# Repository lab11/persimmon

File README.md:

# persimmon
platform to test connectivity of cellular networks around the world

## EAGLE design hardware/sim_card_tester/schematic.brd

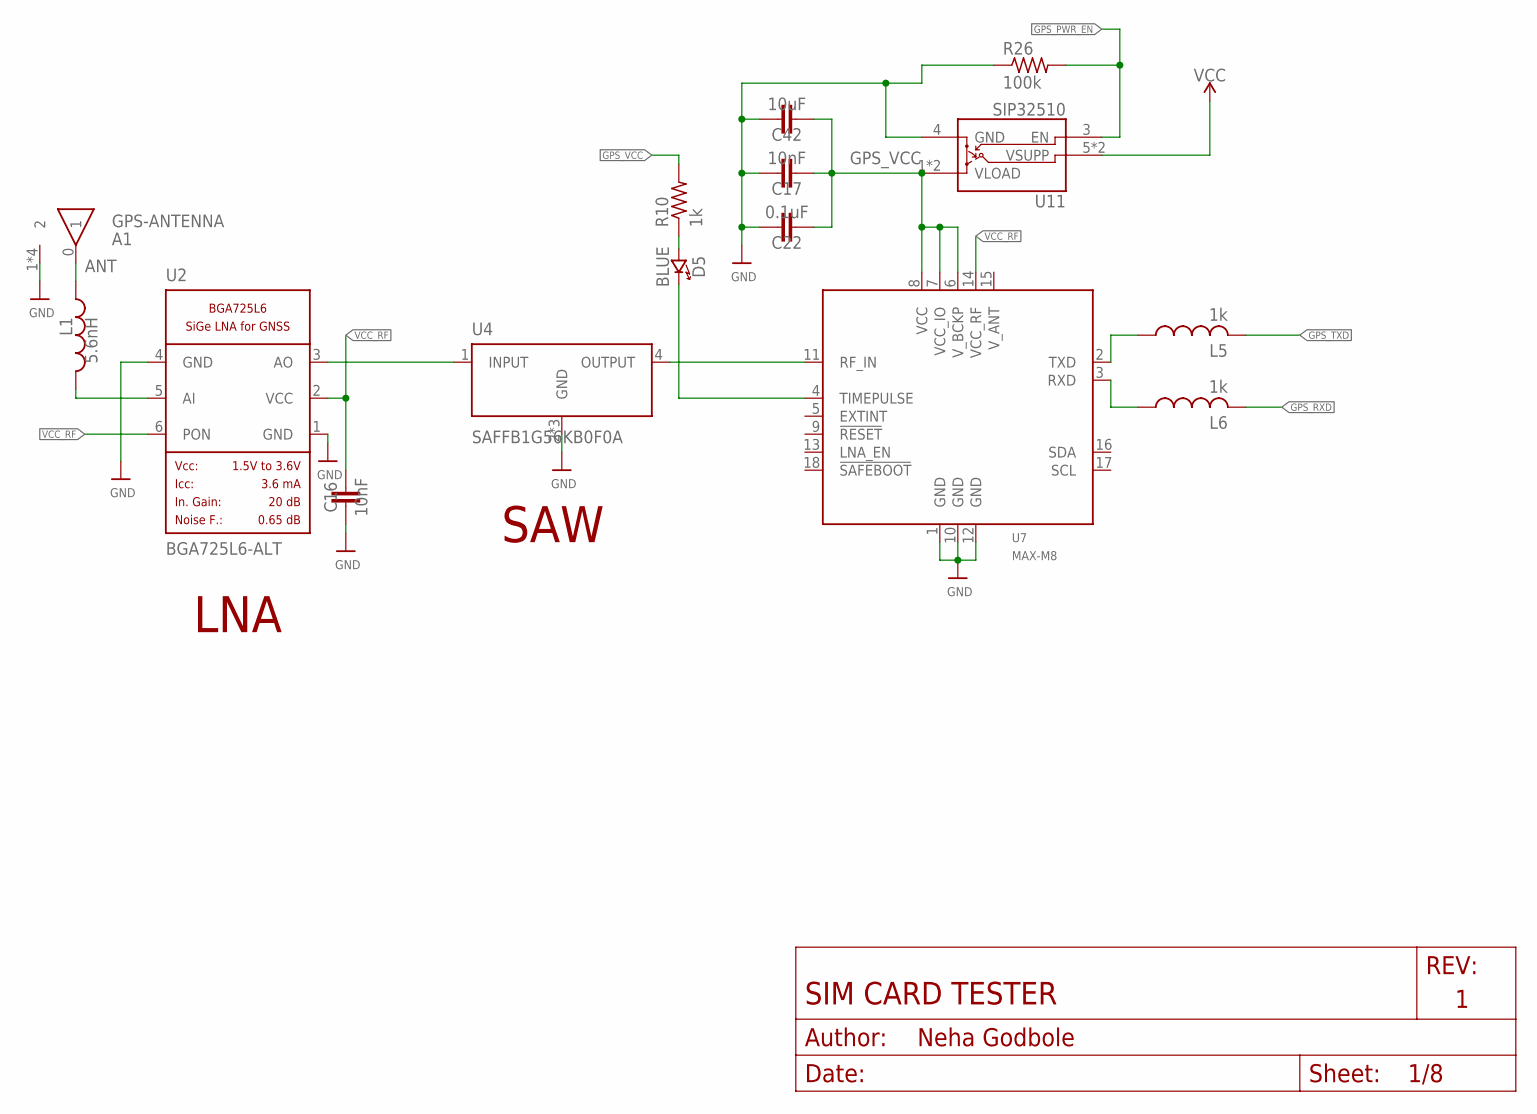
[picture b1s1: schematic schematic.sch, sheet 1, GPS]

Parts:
A1: GPS-ANTENNA; ANT1818B00BT1516S; MPN ANT1818B00BT1516S; DIGIKEY 311-1531-ND
C16, C17: 10nF; RESC0603_L; MPN GRM033R61E103KA12D; DIGIKEY 490-7194-1-ND
C22: 0.1uF; RESC0603_L; MPN GRM033R61A104ME15D; DIGIKEY 490-5405-1-ND
C42: 10uF; RESC0603_L; MPN GRM188R60J106KE47D; DIGIKEY 490-12538-1-ND
D5: BLUE; LED-0603; MPN LTST-C194TBKT; DIGIKEY 160-1837-6-ND
L1: 5.6nH; RESC0603_M; MPN LQW18AN5N6G8ZD; DIGIKEY 490-15723-1-ND
L5, L6: 1k; RESC0603_M; MPN Murata Electronics; DIGIKEY 490-1015-1-ND
R10: 1k; R0603; MPN RC0603JR-071KL; DIGIKEY 311-1.0KGRCT-ND
R26: 100k; R0603; MPN RC0603JR-07100KL; DIGIKEY 311-100KGRCT-ND
U2: BGA725L6-ALT; LNA-TSLP-6-2-ALT; MPN BGA725L6E6327FTSA1; DIGIKEY BGA725L6E6327FTSA1CT-ND
U4: SAFFB1G56KB0F0A; QCS5I; MPN F6QA1G582H2JM-J; DIGIKEY 587-3990-1-ND
U7: MAX-M8; MPN MAX-M8Q-0; DIGIKEY 672-1003-1-ND
U11: SIP32510; TSOT23-6

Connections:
ANT: A1.0 (1), L1.2
GND: A1.1 (2), A1.2, A1.3 (2), A1.4 (2), C16.1, C17.1, C22.1, C42.1, R26.1, U2.1 (GND), U2.4 (GND), U4.2 (GND), U4.3 (GND), U4.5 (GND), U7.1 (GND), U7.10 (GND), U7.12 (GND), U11.4 (GND); also elsewhere on the board
GPS_PWR_EN: R26.2, U11.3 (EN); also elsewhere on the board
GPS_RF_IN: U4.4 (OUTPUT), U7.11 (RF_IN)
GPS_RXD: L6.2; also elsewhere on the board
GPS_TXD: L5.2; also elsewhere on the board
GPS_VCC: C17.2, C22.2, C42.2, R10.2, U7.6 (V_BCKP), U7.7 (VCC_IO), U7.8 (VCC), U11.1 (VLOAD), U11.2 (VLOAD)
LNA_IN: L1.1, U2.5 (AI)
LNA_OUT: U2.3 (AO), U4.1 (INPUT)
unnamed: D5.A (ANODE), R10.1
unnamed: D5.C (CATHODE), U7.4 (TIMEPULSE)
unnamed: L5.1, U7.2 (TXD)
unnamed: L6.1, U7.3 (RXD)
VCC: U11.5 (VSUPP), U11.6 (VSUPP); also elsewhere on the board
VCC_RF: C16.2, U2.2 (VCC), U2.6 (PON), U7.14 (VCC_RF)

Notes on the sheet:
LNA
SAW

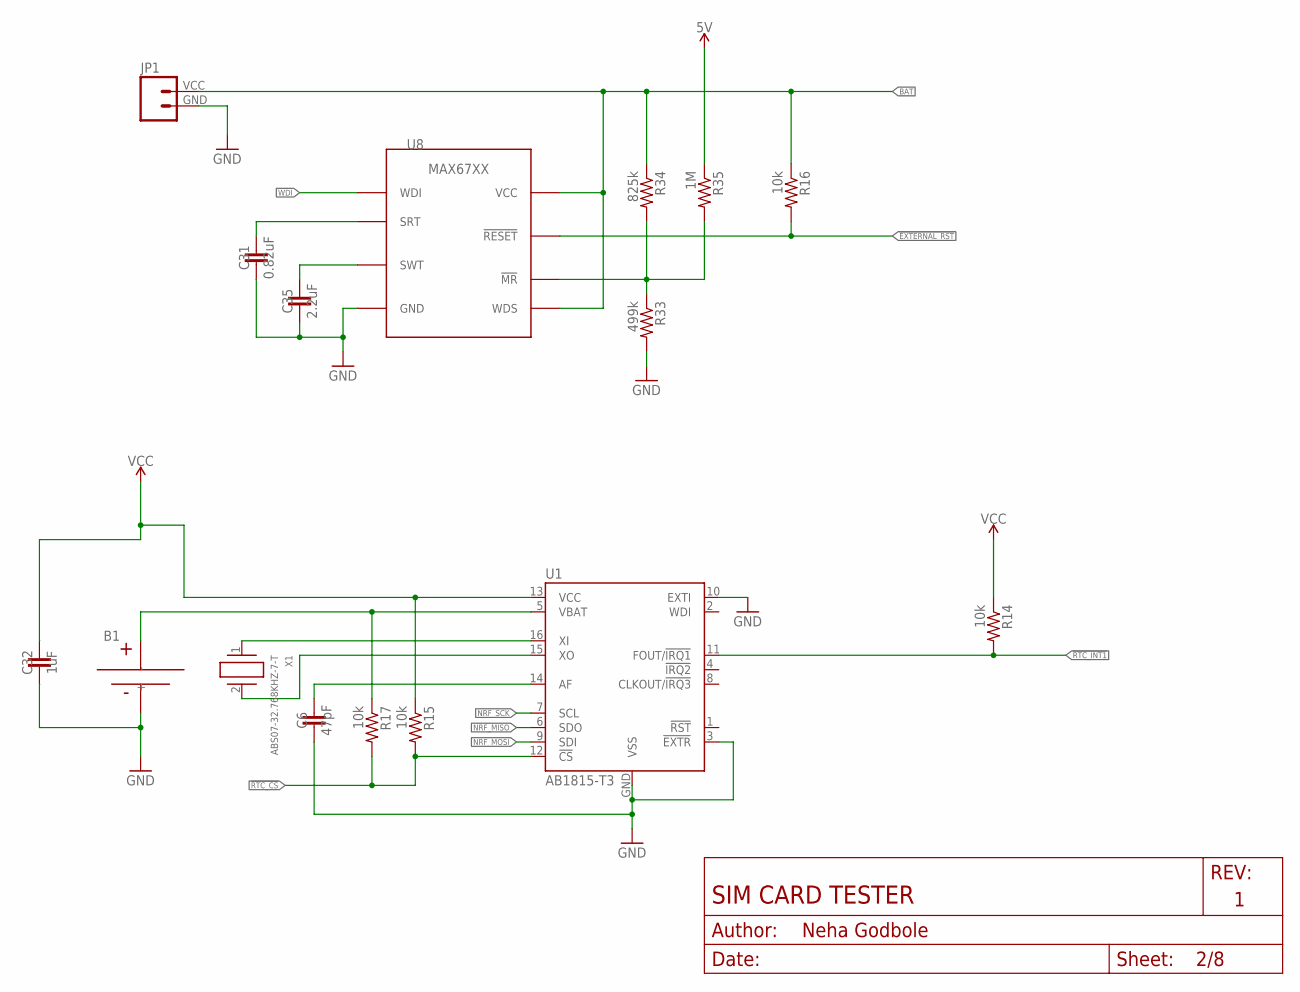
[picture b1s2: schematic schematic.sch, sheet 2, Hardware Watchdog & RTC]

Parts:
B1: MS518SE; MS518SE-FL35E
C6: 47pF; RESC0603_L; MPN C0603C105K8PACTU; DIGIKEY 399-3118-1-ND
C31: 0.82uF; RESC0603_L; MPN C0603C824K8PACTU; DIGIKEY 399-3117-1-ND
C32: 1uF; RESC0603_L; MPN C0603C105K8PACTU; DIGIKEY 399-3118-1-ND
C35: 2.2uF; RESC0603_L; MPN GRM188R61E225MA12D; DIGIKEY 490-12738-1-ND
JP1: M024UCON-15767; JST-2-SMD-VERT; MPN B2B-PH-SM4-TB(LF)(SN); DIGIKEY 455-1734-1-ND
R14, R15, R16, R17: 10k; R0603; MPN RC0603JR-0710KL; DIGIKEY 311-10KGRCT-ND
R33: 499k; R0603; MPN RC0603FR-07499KL; DIGIKEY 311-499KHRCT-ND
R34: 825k; R0603; MPN RC0603FR-07825KL; DIGIKEY 311-825KHRCT-ND
R35: 1M; R0603; MPN RC0603FR-071ML; DIGIKEY 311-1.00MHRCT-ND
U1: AB1815-T3; QFN-16-3MM
U8: MAX67XXMAX6749MAX67XX; SOT-23-8
X1: ABS07-32.768KHZ-7-T; 2-SMD

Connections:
5V: R35.1; also elsewhere on the board
!EXTERNAL_RST: R16.2, U8.7 (!RESET); also elsewhere on the board
!RTC_CS: R15.2, R17.2, U1.12 (!CS); also elsewhere on the board
!RTC_INT1: R14.2, U1.11 (FOUT/!IRQ1); also elsewhere on the board
BAT: JP1.VCC (2), R16.1, R34.1, U8.5 (WDS), U8.8 (VCC); also elsewhere on the board
GND: B1.-, C6.2, C31.2, C32.2, C35.2, JP1.GND (1), R33.2, U1.3 (!EXTR), U1.10 (EXTI), U1.GND (VSS), U8.4 (GND); also elsewhere on the board
unnamed: B1.+, R17.1, U1.5 (VBAT)
unnamed: C6.1, U1.14 (AF)
unnamed: U1.15 (XO), X1.2
unnamed: U1.16 (XI), X1.1
unnamed: R33.1, R34.2, R35.2, U8.1 (!MR)
unnamed: C31.1, U8.3 (SRT)
unnamed: C35.1, U8.2 (SWT)
NRF_MISO: U1.6 (SDO); also elsewhere on the board
NRF_MOSI: U1.9 (SDI); also elsewhere on the board
NRF_SCK: U1.7 (SCL); also elsewhere on the board
VCC: C32.1, R14.1, R15.1, U1.13 (VCC); also elsewhere on the board
WDI: U8.6 (WDI); also elsewhere on the board

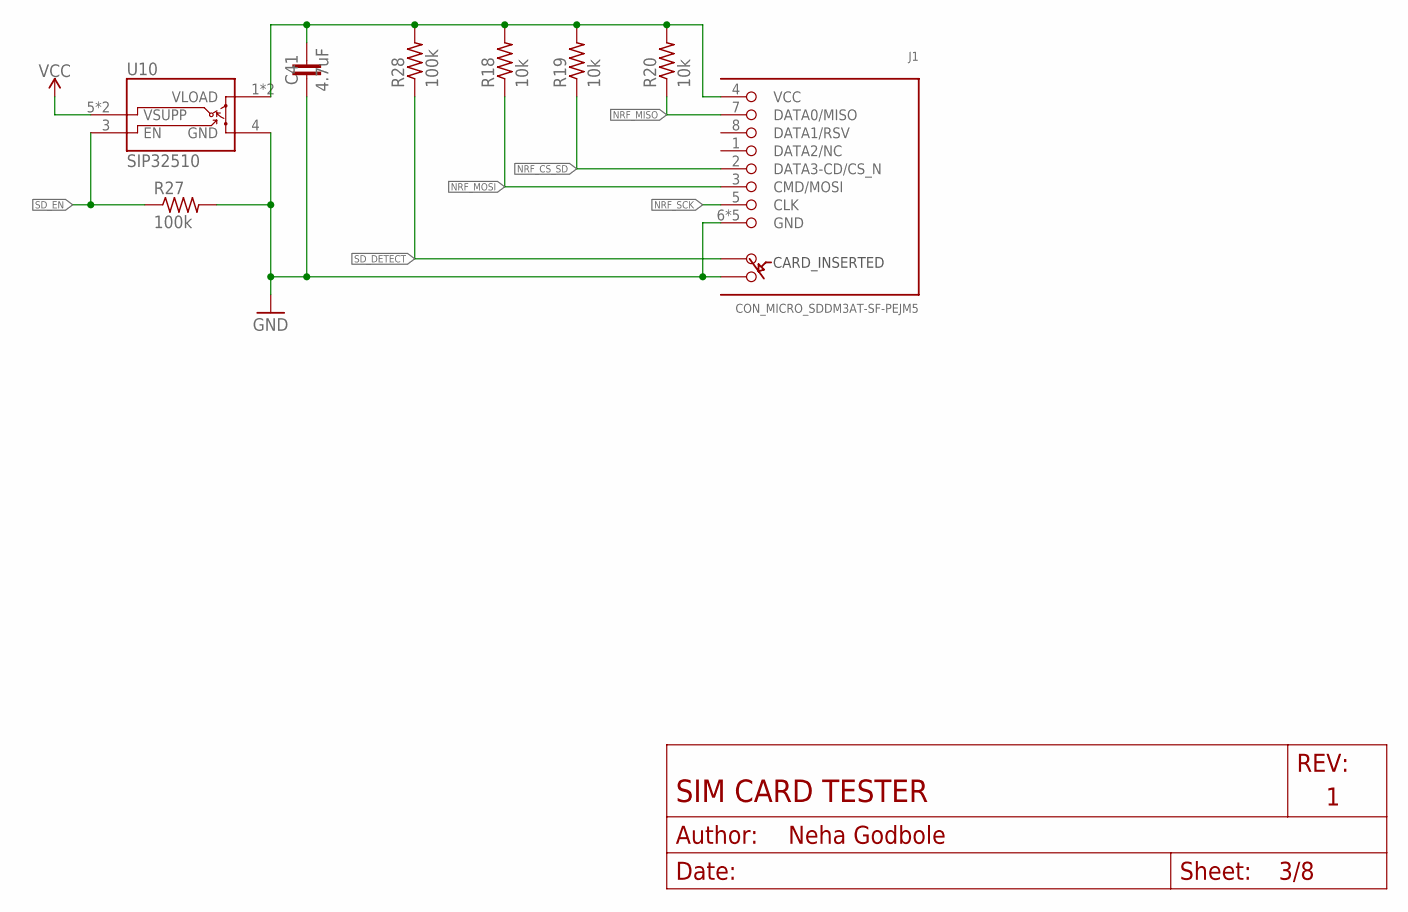
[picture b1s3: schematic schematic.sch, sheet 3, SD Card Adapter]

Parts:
C41: 4.7uF; RESC0603_L; MPN ZRB18AR6YA475KE05L; DIGIKEY 490-10992-1-ND
J1: CON_MICRO_SDDM3AT-SF-PEJM5; DM3AT-SF-PEJM5; MPN DM3AT-SF-PEJM5
R18, R19, R20: 10k; R0603; MPN RC0603JR-0710KL; DIGIKEY 311-10KGRCT-ND
R27, R28: 100k; R0603; MPN RC0603JR-07100KL; DIGIKEY 311-100KGRCT-ND
U10: SIP32510; TSOT23-6

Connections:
!NRF_CS_SD: J1.2 (DATA3-CD/CS_N), R19.1; also elsewhere on the board
!SD_DETECT: J1.A, R28.1; also elsewhere on the board
GND: C41.2, J1.6 (GND), J1.B, J1.MOUNT0 (GND), J1.MOUNT1 (GND), J1.MOUNT2 (GND), J1.MOUNT3 (GND), R27.2, U10.4 (GND); also elsewhere on the board
unnamed: C41.1, J1.4 (VCC), R18.2, R19.2, R20.2, R28.2, U10.1 (VLOAD), U10.2 (VLOAD)
NRF_MISO: J1.7 (DATA0/MISO), R20.1; also elsewhere on the board
NRF_MOSI: J1.3 (CMD/MOSI), R18.1; also elsewhere on the board
NRF_SCK: J1.5 (CLK); also elsewhere on the board
SD_EN: R27.1, U10.3 (EN); also elsewhere on the board
VCC: U10.5 (VSUPP), U10.6 (VSUPP); also elsewhere on the board

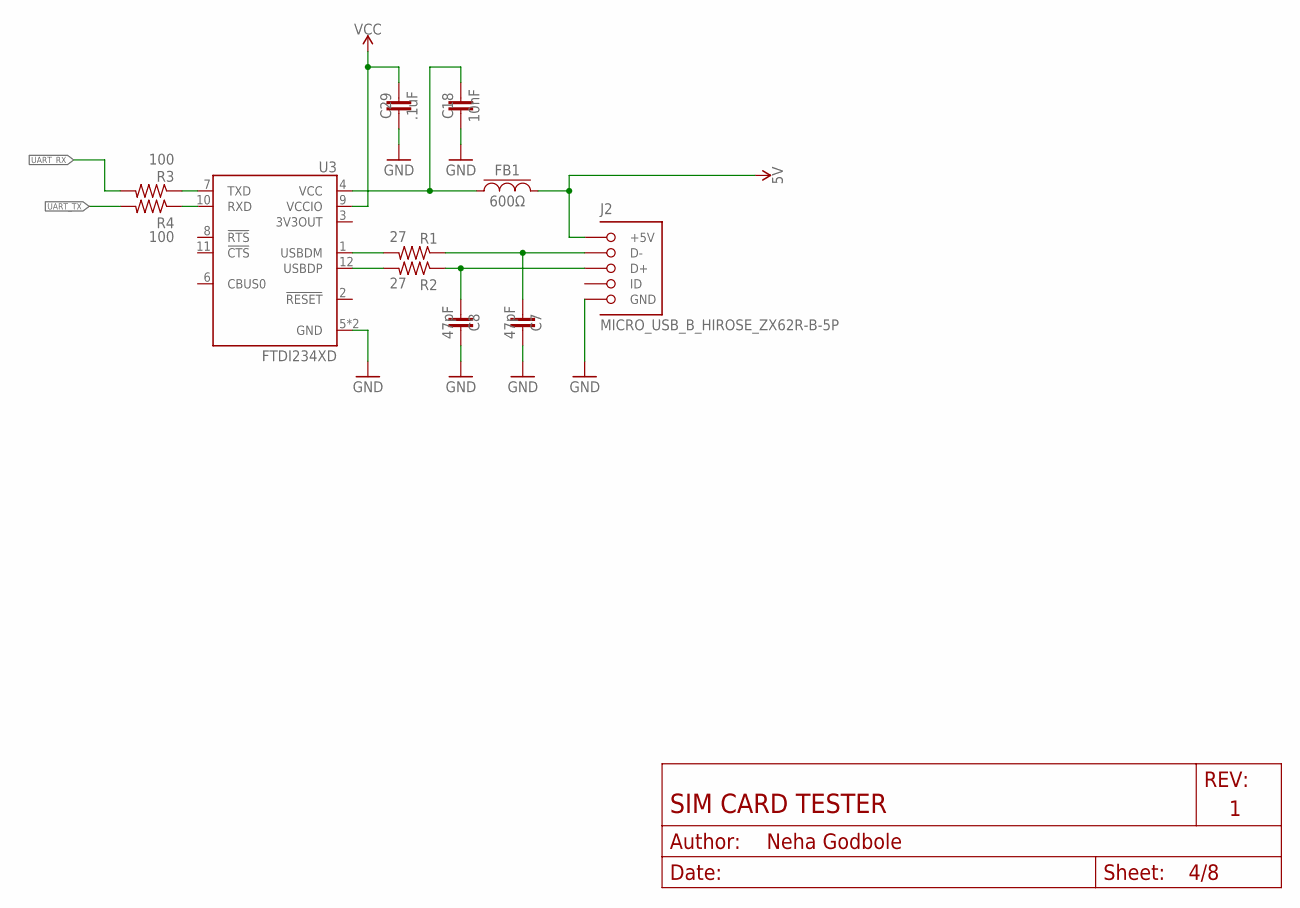
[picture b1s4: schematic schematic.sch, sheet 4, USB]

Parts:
C7, C8: 47pF; RESC0603_L; MPN CC0603JRNPO9BN470; DIGIKEY 311-1065-1-ND
C18: 10nF; RESC0603_L; MPN GRM033R61E103KA12D; DIGIKEY 490-7194-1-ND
C29: .1uF; RESC0603_L; MPN GRM033R61A104ME15D; DIGIKEY 490-5405-1-ND
FB1: 600Ω; 0805_CAP; DIGIKEY 240-2390-1-ND
J2: MICRO_USB_B_HIROSE_ZX62R-B-5P; USB_MICRO_B-HIROSE-ZX62R-B-5P; DIGIKEY H125274CT-ND
R1, R2: 27; R0603; MPN RC0603JR-0727RL; DIGIKEY 311-27GRCT-ND
R3, R4: 100; R0603; MPN RC0603FR-07100RL; DIGIKEY 311-100HRCT-ND
U3: FTDI234XD; DFN-12/3MM

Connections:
5V: FB1.P$2, J2.1 (+5V); also elsewhere on the board
D+: C8.1, J2.3 (D+), R2.1
D-: C7.1, J2.2 (D-), R1.1
GND: C7.2, C8.2, C18.2, C29.2, J2.5 (GND), U3.5 (GND), U3.13 (GND); also elsewhere on the board
unnamed: R1.2, U3.1 (USBDM)
unnamed: R2.2, U3.12 (USBDP)
unnamed: R4.1, U3.10 (RXD)
unnamed: R3.1, U3.7 (TXD)
unnamed: C18.1, FB1.P$1, U3.4 (VCC)
UART_RX: R3.2; also elsewhere on the board
UART_TX: R4.2; also elsewhere on the board
VCC: C29.1, U3.9 (VCCIO); also elsewhere on the board

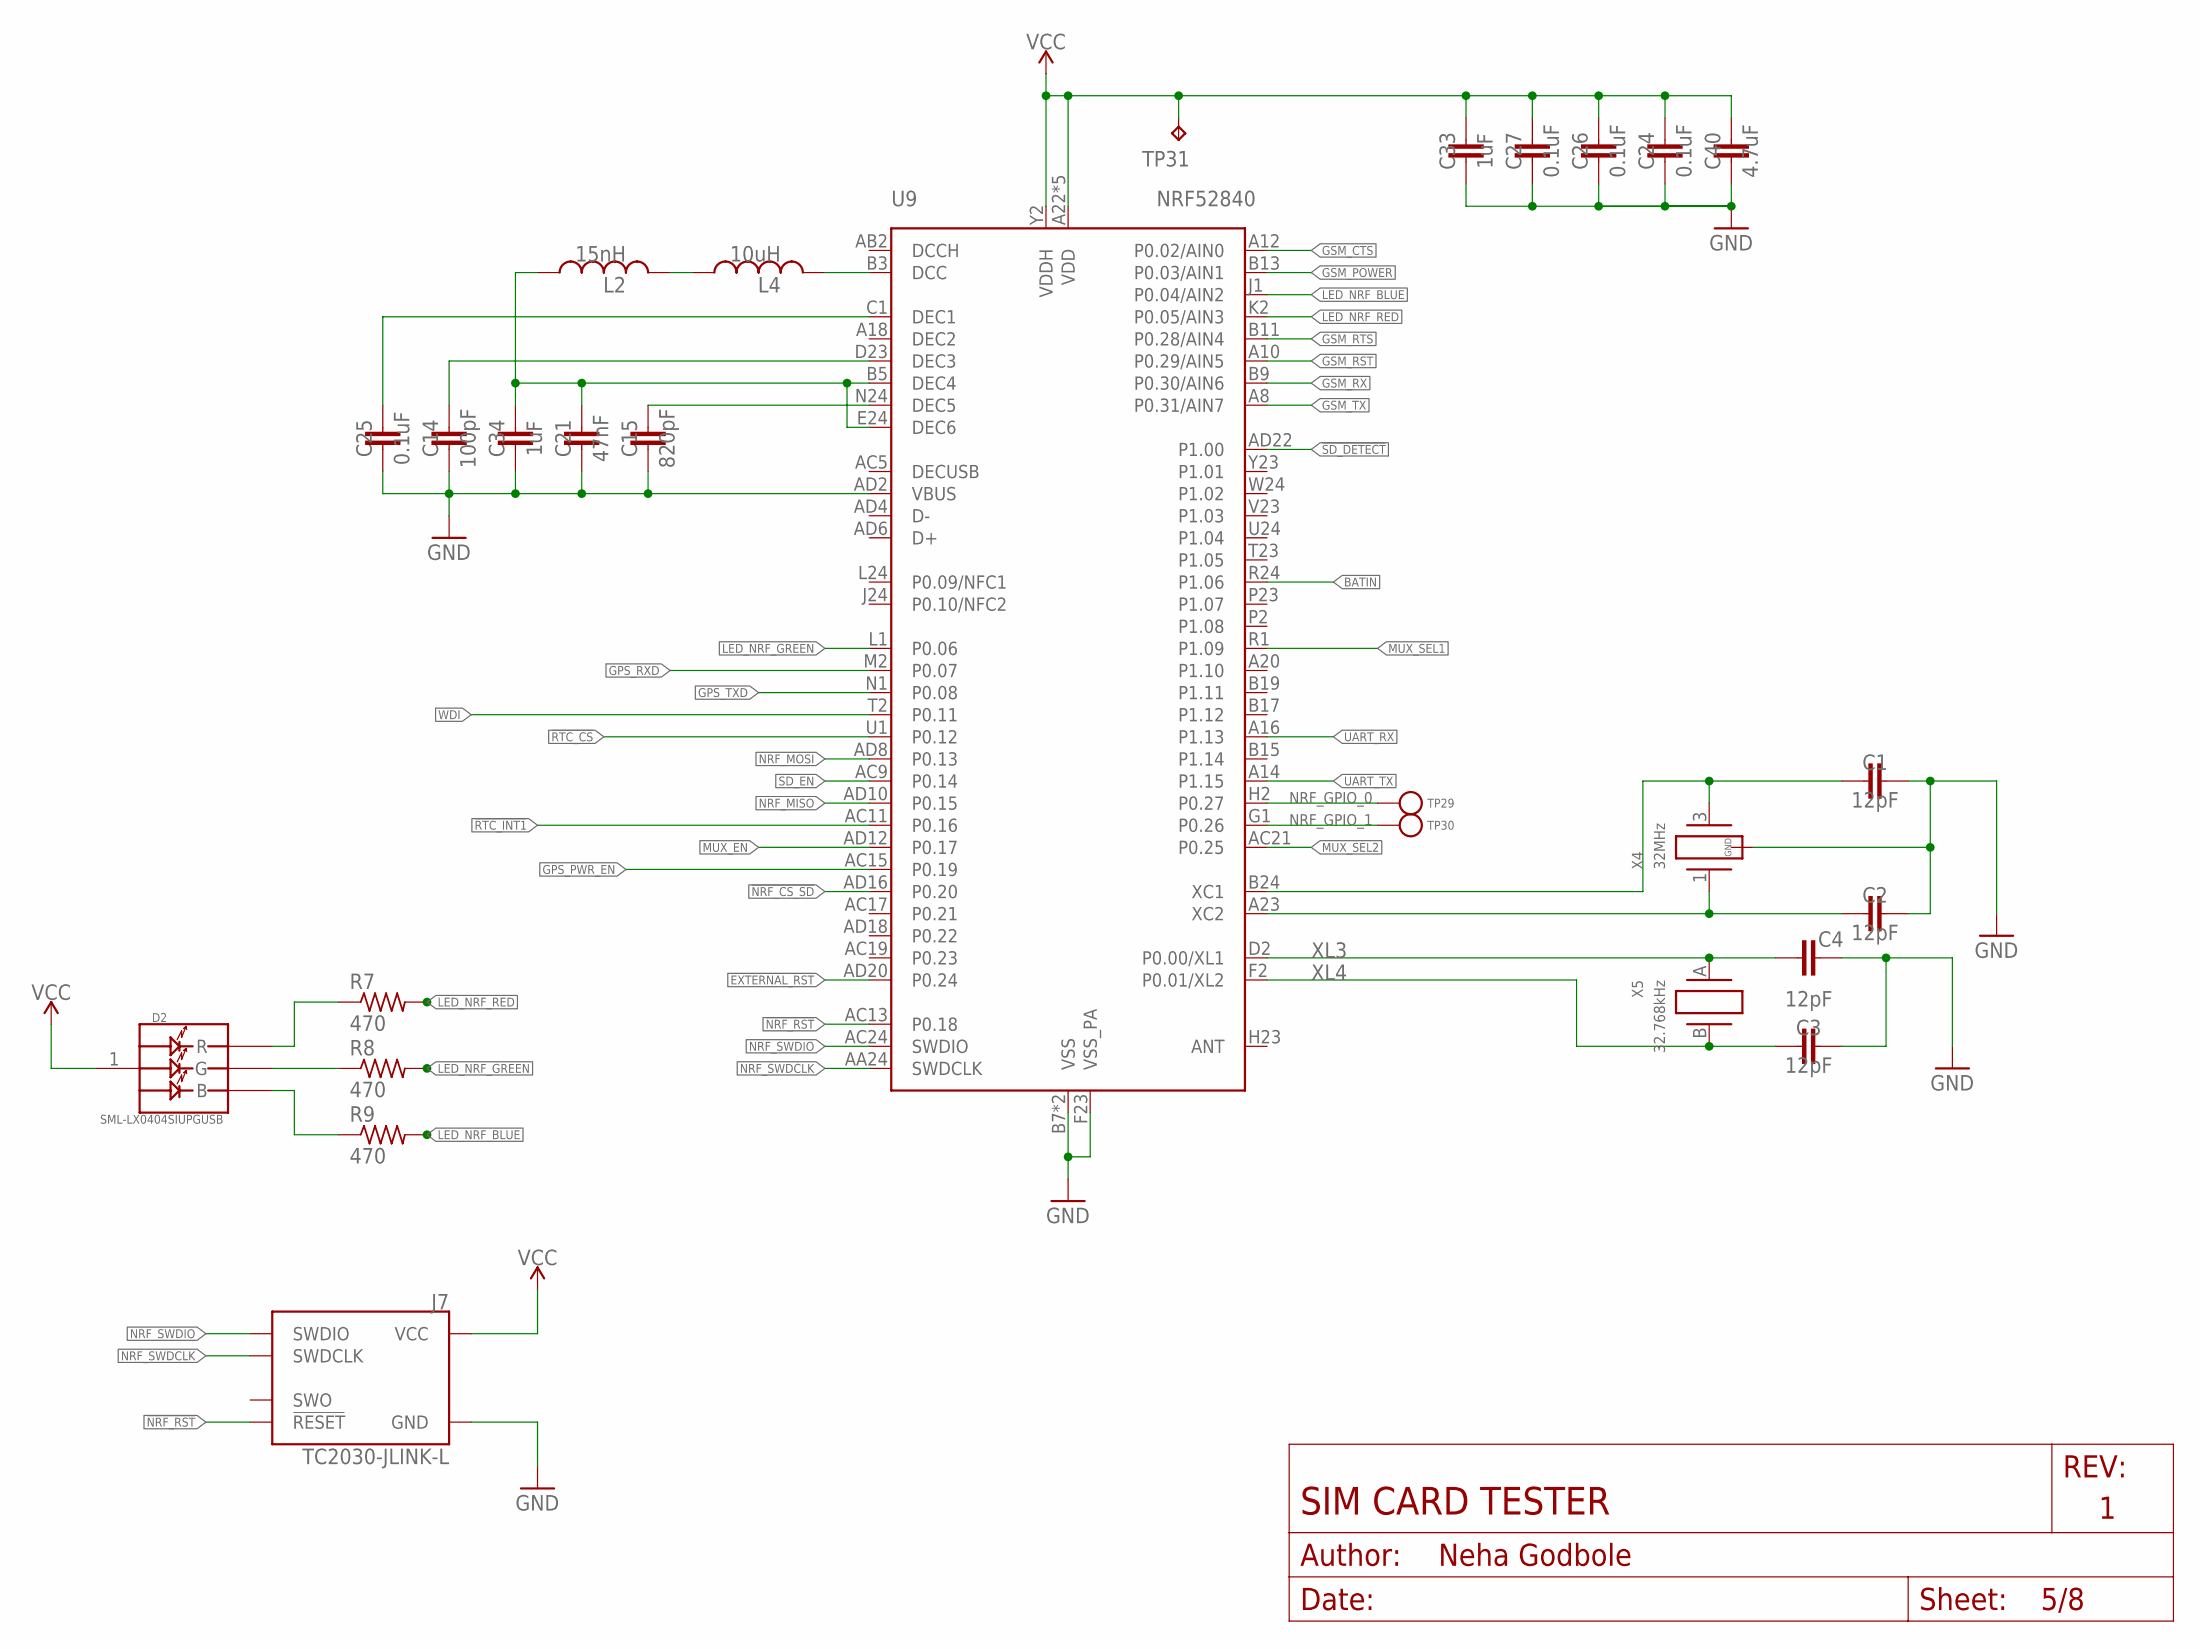
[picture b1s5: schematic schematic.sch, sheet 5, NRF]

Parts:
C1, C2, C3, C4: 12pF; RESC0603_L; MPN CC0603JRNPO9BN120; DIGIKEY 311-1059-1-ND
C14: 100pF; RESC0603_L; MPN CC0603JRNPO9BN101; DIGIKEY 311-1069-1-ND
C15: 820pF; RESC0603_L; MPN CC0603KRX7R9BB821; DIGIKEY 311-1189-1-ND
C21: 47nF; RESC0603_L; MPN GCJ188R71H473KA12D; DIGIKEY 490-5854-1-ND
C24, C25, C26, C27: 0.1uF; RESC0603_L; MPN GRM033R61A104ME15D; DIGIKEY 490-5405-1-ND
C33, C34: 1uF; RESC0603_L; MPN C0603C105K8PACTU; DIGIKEY 399-3118-1-ND
C40: 4.7uF; RESC0603_L; MPN ZRB18AR6YA475KE05L; DIGIKEY 490-10992-1-ND
D2: SML-LX0404SIUPGUSB; 1MM_SQ_4PAD
J7: TC2030-JLINK-L; TC2030-IDC
L2: 15nH; RESC0603_M; MPN LQW18AN15NG8ZD; DIGIKEY 490-15648-1-ND
L4: 10uH; RESC0603_M; MPN CBMF1608T100K; DIGIKEY 587-1720-1-ND
R7, R8, R9: 470; R0603; MPN RC0603FR-07470RL; DIGIKEY 311-470HRCT-ND
TP29, TP30: TEST-POINT; PAD.03X.03
TP31: TPTP06SQ; TP06SQ
U9: NRF52840; AQFN73
X4: 32MHz; TXC-7V
X5: 32.768kHz; ABS05

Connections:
!EXTERNAL_RST: U9.AD20 (P0.24); also elsewhere on the board
!NRF_CS_SD: U9.AD16 (P0.20); also elsewhere on the board
!NRF_RST: J7.3 (!RESET), U9.AC13 (P0.18); also elsewhere on the board
!RTC_CS: U9.U1 (P0.12); also elsewhere on the board
!RTC_INT1: U9.AC11 (P0.16); also elsewhere on the board
!SD_DETECT: U9.AD22 (P1.00); also elsewhere on the board
BATIN: U9.R24 (P1.06); also elsewhere on the board
GND: C1.1, C2.1, C3.1, C4.1, C14.2, C15.2, C21.2, C24.2, C25.2, C26.2, C27.2, C33.2, C34.2, C40.2, J7.5 (GND), U9.AD2 (VBUS), U9.B7 (VSS), U9.F23 (VSS_PA), U9.GND (VSS), X4.2 (GND), X4.4 (GND); also elsewhere on the board
GPS_PWR_EN: U9.AC15 (P0.19); also elsewhere on the board
GPS_RXD: U9.M2 (P0.07); also elsewhere on the board
GPS_TXD: U9.N1 (P0.08); also elsewhere on the board
GSM_CTS: U9.A12 (P0.02/AIN0); also elsewhere on the board
GSM_POWER: U9.B13 (P0.03/AIN1); also elsewhere on the board
GSM_RST: U9.A10 (P0.29/AIN5); also elsewhere on the board
GSM_RTS: U9.B11 (P0.28/AIN4); also elsewhere on the board
GSM_RX: U9.B9 (P0.30/AIN6); also elsewhere on the board
GSM_TX: U9.A8 (P0.31/AIN7); also elsewhere on the board
LED_NRF_BLUE: R9.2, U9.J1 (P0.04/AIN2)
LED_NRF_GREEN: R8.2, U9.L1 (P0.06)
LED_NRF_RED: R7.2, U9.K2 (P0.05/AIN3)
MUX_EN: U9.AD12 (P0.17); also elsewhere on the board
MUX_SEL1: U9.R1 (P1.09); also elsewhere on the board
MUX_SEL2: U9.AC21 (P0.25); also elsewhere on the board
unnamed: C25.1, U9.C1 (DEC1)
unnamed: C21.1, C34.1, L2.1, U9.B5 (DEC4), U9.E24 (DEC6)
unnamed: C14.1, U9.D23 (DEC3)
unnamed: C1.2, U9.B24 (XC1), X4.3 (2)
unnamed: C2.2, U9.A23 (XC2), X4.1
unnamed: L4.2, U9.B3 (DCC)
unnamed: L2.2, L4.1
unnamed: C15.1, U9.N24 (DEC5)
unnamed: D2.2 (R), R7.1
unnamed: D2.4 (G), R8.1
unnamed: D2.3 (B), R9.1
NRF_GPIO_0: TP29.P$1, U9.H2 (P0.27)
NRF_GPIO_1: TP30.P$1, U9.G1 (P0.26)
NRF_MISO: U9.AD10 (P0.15); also elsewhere on the board
NRF_MOSI: U9.AD8 (P0.13); also elsewhere on the board
NRF_SWDCLK: J7.4 (SWDCLK), U9.AA24 (SWDCLK); also elsewhere on the board
NRF_SWDIO: J7.2 (SWDIO), U9.AC24 (SWDIO); also elsewhere on the board
SD_EN: U9.AC9 (P0.14); also elsewhere on the board
UART_RX: U9.A16 (P1.13); also elsewhere on the board
UART_TX: U9.A14 (P1.15); also elsewhere on the board
VCC: C24.1, C26.1, C27.1, C33.1, C40.1, D2.1 (VDD), J7.1 (VCC), TP31.TP, U9.A22 (VDD), U9.AD14 (VDD), U9.AD23 (VDD), U9.B1 (VDD), U9.W1 (VDD), U9.Y2 (VDDH); also elsewhere on the board
WDI: U9.T2 (P0.11); also elsewhere on the board
XL3: C4.2, U9.D2 (P0.00/XL1), X5.A (1)
XL4: C3.2, U9.F2 (P0.01/XL2), X5.B (2)

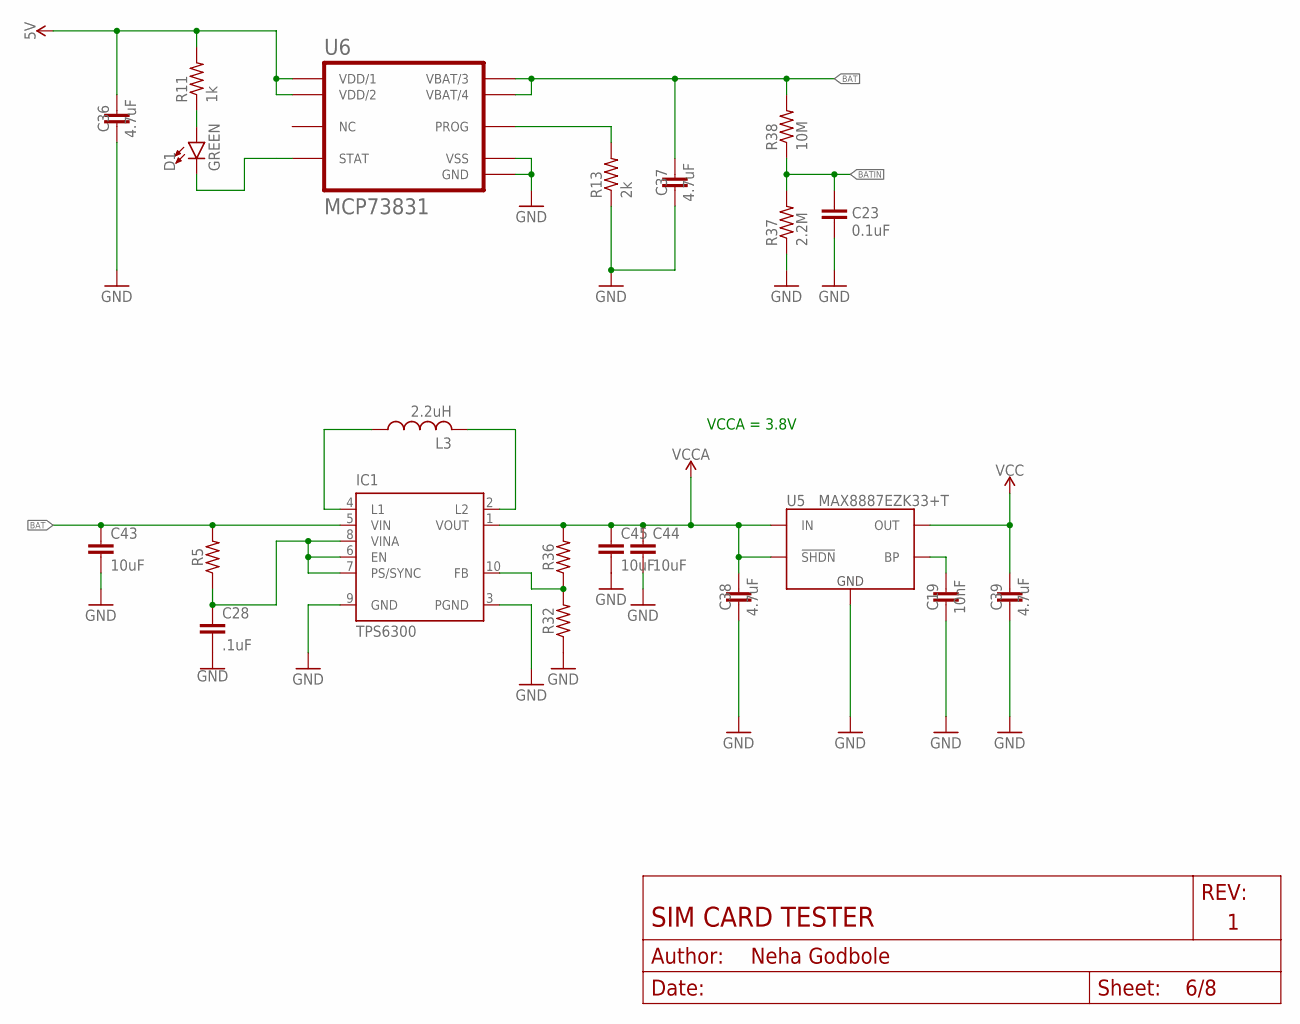
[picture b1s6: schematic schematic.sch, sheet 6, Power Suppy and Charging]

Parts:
C19: 10nF; RESC0603_L; MPN GRM033R61E103KA12D; DIGIKEY 490-7194-1-ND
C23: 0.1uF; RESC0603_L; MPN GRM033R61A104ME15D; DIGIKEY 490-5405-1-ND
C28: .1uF; RESC0603_L; MPN GRM033R61A104ME15D; DIGIKEY 490-5405-1-ND
C36, C37, C38, C39: 4.7uF; RESC0603_L; MPN ZRB18AR6YA475KE05L; DIGIKEY 490-10992-1-ND
C43, C44, C45: 10uF; RESC0603_L; MPN GRM188R60J106KE47D; DIGIKEY 490-12538-1-ND
D1: GREEN; LED-0603
IC1: TPS6300; DRC-S-PVSON-N10
L3: 2.2uH; RESC0603_M; MPN LQM18PN2R2MGHD; DIGIKEY 490-14478-1-ND
R5: 100; R0603; MPN RC0603FR-07100RL; DIGIKEY 311-100HRCT-ND
R11: 1k; R0603; MPN RC0603JR-071KL; DIGIKEY 311-1.0KGRCT-ND
R13: 2k; R0603; MPN RC0603FR-072KL; DIGIKEY 311-2.00KHRCT-ND
R32: 200k; R0603; MPN RC0603JR-07200KL; DIGIKEY 311-200KGRTR-ND
R36: 1.3M; R0603; MPN RC0603FR-071M3L; DIGIKEY YAG3326CT-ND
R37: 2.2M; R0603; MPN RC0603JR-072M2L; DIGIKEY 311-2.2MGRCT-ND
R38: 10M; R0603; MPN RC0603JR-0710ML; DIGIKEY 311-10MGRCT-ND
U5: MAX8887EZK33+T; SOT-23-5
U6: MCP73831; DFN-8-MCP

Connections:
5V: C36.1, R11.2, U6.1 (VDD/1), U6.2 (VDD/2); also elsewhere on the board
!CHRG: D1.A, R11.1
BAT: C37.1, C43.1, IC1.5 (VIN), R5.2, R38.2, U6.3 (VBAT/3), U6.4 (VBAT/4); also elsewhere on the board
BATIN: C23.2, R37.2, R38.1; also elsewhere on the board
GND: C19.2, C23.1, C28.2, C36.2, C37.2, C38.2, C39.2, C43.2, C44.2, C45.2, IC1.3 (PGND), IC1.9 (GND), R13.1, R32.1, R37.1, U5.2 (GND), U6.6 (VSS), U6.GND; also elsewhere on the board
unnamed: R13.2, U6.8 (PROG)
unnamed: D1.C, U6.5 (STAT)
unnamed: IC1.4 (L1), L3.1
unnamed: IC1.2 (L2), L3.2
unnamed: C28.1, IC1.6 (EN), IC1.7 (PS/SYNC), IC1.8 (VINA), R5.1
unnamed: IC1.10 (FB), R32.2, R36.1
unnamed: C19.1, U5.4 (BP)
VCC: C39.1, U5.5 (OUT); also elsewhere on the board
VCCA: C38.1, C44.1, C45.1, IC1.1 (VOUT), R36.2, U5.1 (IN), U5.3 (!SHDN); also elsewhere on the board

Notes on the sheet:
VCCA = 3.8V

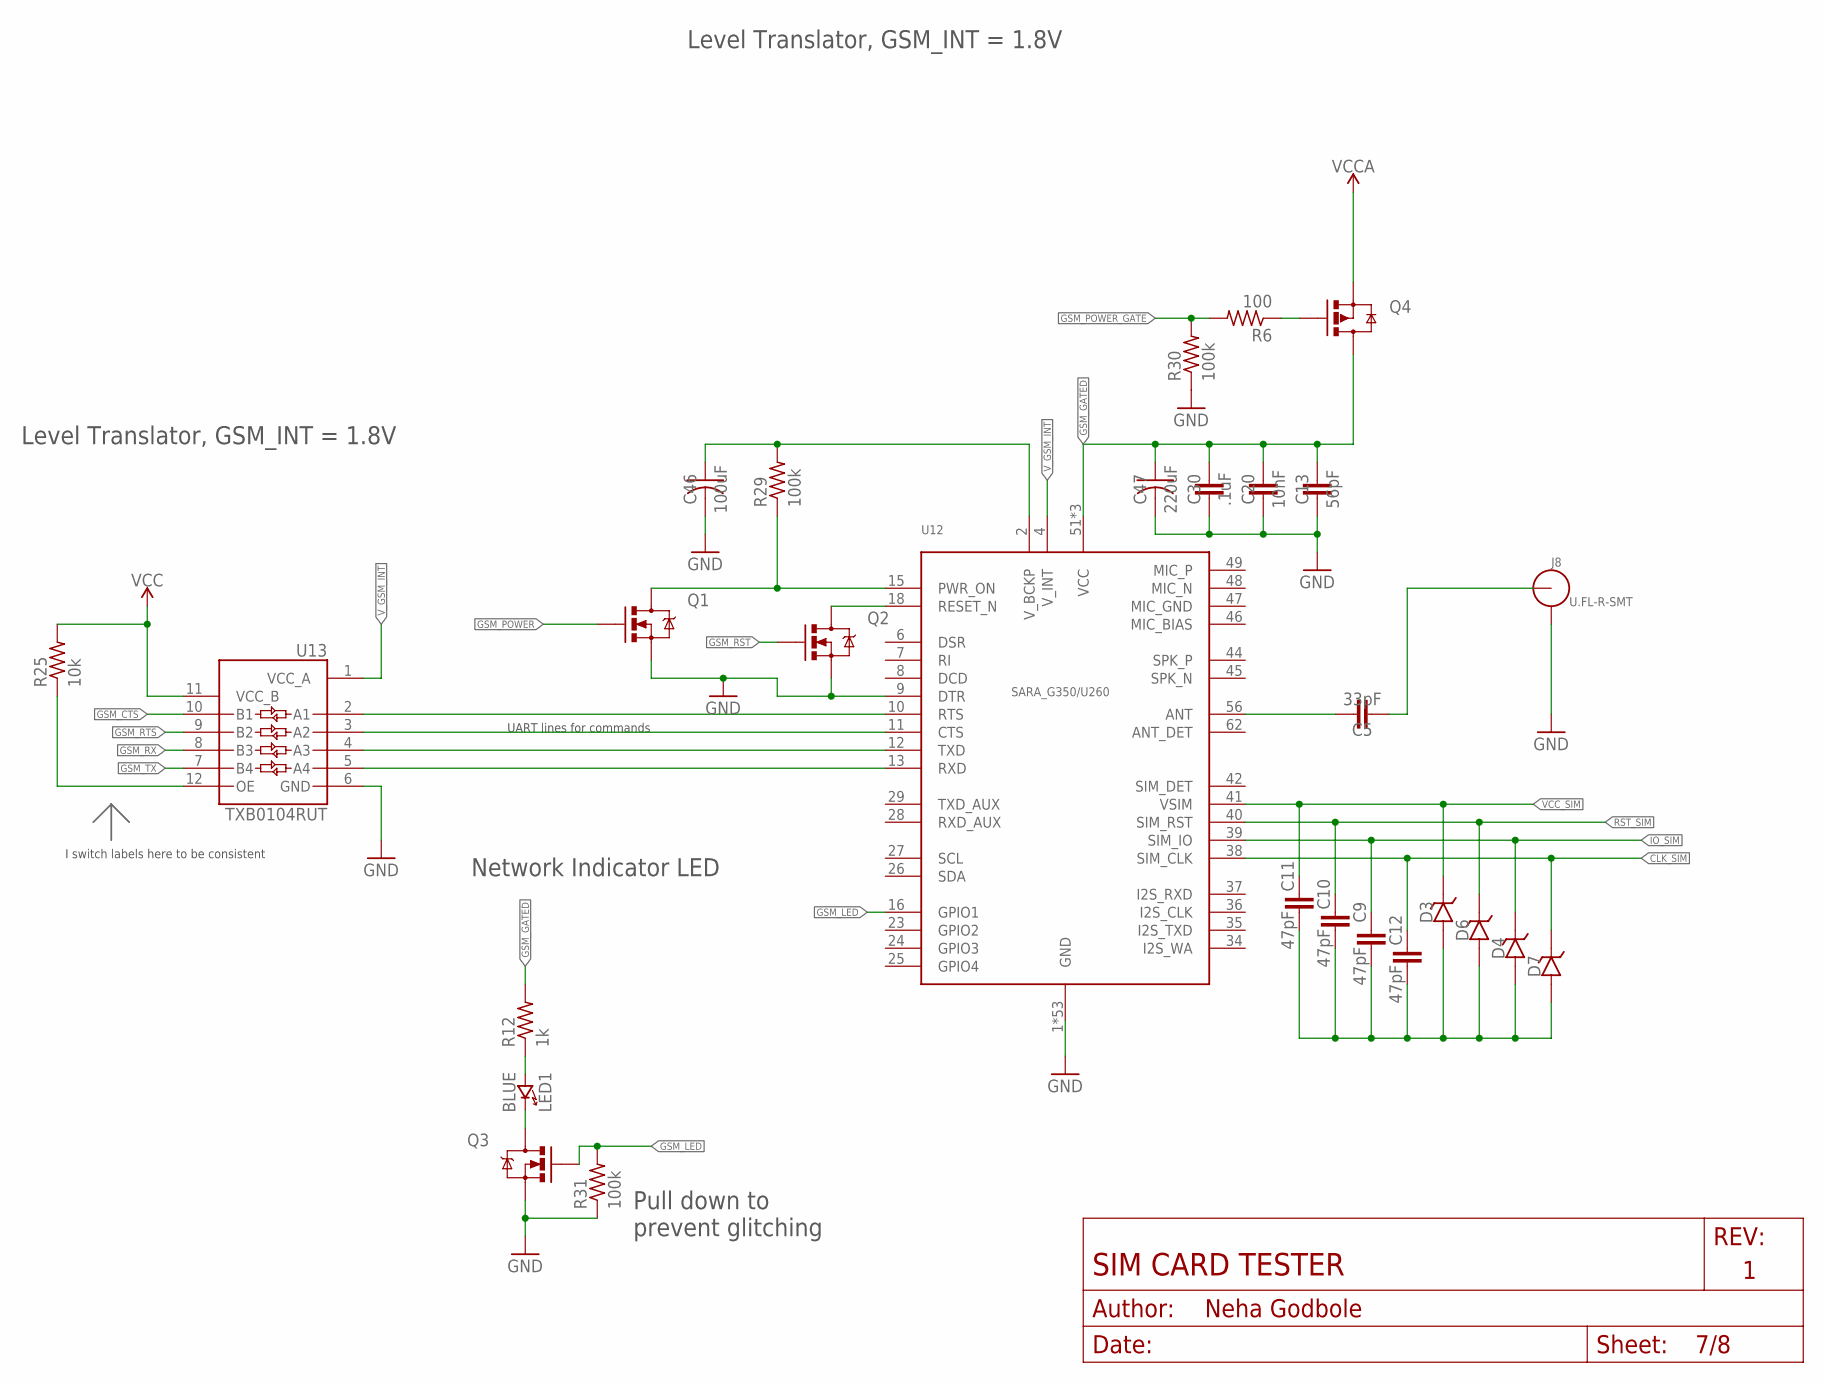
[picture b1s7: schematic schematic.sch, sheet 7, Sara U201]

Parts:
C5: 33pF; RESC0603_L; MPN C0603C330J1GACTU; DIGIKEY 399-7896-1-ND
C9, C10, C11, C12: 47pF; RESC0603_L; MPN CC0603JRNPO9BN470; DIGIKEY 311-1065-1-ND
C13: 56pF; RESC0603_L; MPN CC0603JRNPO9BN560; DIGIKEY 311-1066-1-ND
C20: 10nF; RESC0603_L; MPN GRM033R61E103KA12D; DIGIKEY 490-7194-1-ND
C30: .1uF; RESC0603_L; MPN GRM033R61A104ME15D; DIGIKEY 490-5405-1-ND
C46: 100uF; C1210; MPN GRM32ER61A107ME20L; DIGIKEY 490-9969-1-ND
C47: 220uF; C1210; MPN GRM32ER60J227ME05L; DIGIKEY 490-16308-1-ND
D3, D4, D6, D7: 14V; 0402_DIODE; MPN PESD0402-140; DIGIKEY PESD0402-140CT-ND
J8: U.FL-R-SMT; U.FL_SMT
LED1: BLUE; LED-0603; MPN SML-D12M8WT86; DIGIKEY 511-1578-1-ND
Q1, Q2, Q3: MOSFET-NCHANNELSMD; SOT23-3; MPN 2N7002LT1G; DIGIKEY 2N7002LT1GOSCT-ND
Q4: SI223DDS; SOT23-3
R6: 100; R0603; MPN RC0603FR-07100RL; DIGIKEY 311-100HRCT-ND
R12: 1k; R0603; MPN RC0603JR-071KL; DIGIKEY 311-1.0KGRCT-ND
R25: 10k; R0603; MPN RC0603JR-0710KL; DIGIKEY 311-10KGRCT-ND
R29, R30, R31: 100k; R0603; MPN RC0603JR-07100KL; DIGIKEY 311-100KGRCT-ND
U12: UBLOX_SARA_G350; UBLOX_SARA_G3
U13: TXB0104RUT; UQFN-12

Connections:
CLK_SIM: C12.1, D7.CATHODE, U12.38 (SIM_CLK); also elsewhere on the board
GND: C13.2, C20.2, C30.2, C46.2, C47.2, J8.GND1, J8.GND2, Q1.2 (S), Q2.2 (S), Q3.2 (S), R30.1, R31.1, U12.1 (GND), U12.3 (GND), U12.5 (GND), U12.9 (DTR), U12.14 (GND), U12.20 (GND), U12.21 (GND), U12.22 (GND), U12.30 (GND), U12.32 (GND), U12.33 (GND), U12.43 (GND), U12.50 (GND), U12.54 (GND), U12.55 (GND), U12.57 (GND), U12.58 (GND), U12.59 (GND), U12.60 (GND), U12.61 (GND), U12.63 (GND), U12.64 (GND), U12.65 (GND), U12.66 (GND), U12.67 (GND), U12.68 (GND), U12.69 (GND), U12.70 (GND), U12.71 (GND), U12.72 (GND), U12.73 (GND), U12.74 (GND), U12.75 (GND), U12.76 (GND), U12.77 (GND), U12.78 (GND), U12.79 (GND), U12.80 (GND), U12.81 (GND), U12.82 (GND), U12.83 (GND), U12.84 (GND), U12.85 (GND), U12.86 (GND), U12.87 (GND), U12.88 (GND), U12.89 (GND), U12.90 (GND), U12.91 (GND), U12.92 (GND), U12.93 (GND), U12.94 (GND), U12.95 (GND), U12.96 (GND), U13.6 (GND); also elsewhere on the board
GSM_CTS: U13.10 (B1); also elsewhere on the board
GSM_GATED: C13.1, C20.1, C30.1, C47.1, Q4.3 (D), R12.2, U12.51 (VCC), U12.52 (VCC), U12.53 (VCC)
GSM_LED: Q3.1 (G), R31.2, U12.16 (GPIO1)
GSM_POWER: Q1.1 (G); also elsewhere on the board
GSM_POWER_GATE: R6.2, R30.2
GSM_RST: Q2.1 (G); also elsewhere on the board
GSM_RTS: U13.9 (B2); also elsewhere on the board
GSM_RX: U13.8 (B3); also elsewhere on the board
GSM_TX: U13.7 (B4); also elsewhere on the board
IO_SIM: C9.1, D4.CATHODE, U12.39 (SIM_IO); also elsewhere on the board
unnamed: U12.12 (TXD), U13.4 (A3)
unnamed: U12.13 (RXD), U13.5 (A4)
unnamed: LED1.C (CATHODE), Q3.3 (D)
unnamed: Q2.3 (D), U12.18 (RESET_N)
unnamed: C46.1, R29.2, U12.2 (V_BCKP)
unnamed: Q1.3 (D), R29.1, U12.15 (PWR_ON)
unnamed: LED1.A (ANODE), R12.1
unnamed: U12.11 (CTS), U13.3 (A2)
unnamed: U12.10 (RTS), U13.2 (A1)
unnamed: Q4.1 (G), R6.1
unnamed: R25.1, U13.12 (OE)
unnamed: C5.1, U12.56 (ANT)
unnamed: C5.2, J8.SIG (ANT)
unnamed: C9.2, C10.2, C11.2, C12.2, D3.ANODE, D4.ANODE, D6.ANODE, D7.ANODE
RST_SIM: C10.1, D6.CATHODE, U12.40 (SIM_RST); also elsewhere on the board
VCC: R25.2, U13.11 (VCC_B); also elsewhere on the board
VCCA: Q4.2 (S); also elsewhere on the board
VCC_SIM: C11.1, D3.CATHODE, U12.41 (VSIM); also elsewhere on the board
V_GSM_INT: U12.4 (V_INT), U13.1 (VCC_A)

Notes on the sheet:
Level Translator, GSM_INT = 1.8V
I switch labels here to be consistent
UART lines for commands
Network Indicator LED
Pull down to prevent glitching

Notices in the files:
parts and their libraries:
SparkFun-LED: Licensing: CC v3.0 Share-Alike You are welcome to use this library for commercial purposes.
SparkFun-PowerSymbols: Licensing: Creative Commons ShareAlike 4.0 International - https://creativecommons.org/licenses/by-sa/4.0
